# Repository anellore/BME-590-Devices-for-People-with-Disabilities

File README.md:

# BME-590-Devices-for-People-with-Disabilities

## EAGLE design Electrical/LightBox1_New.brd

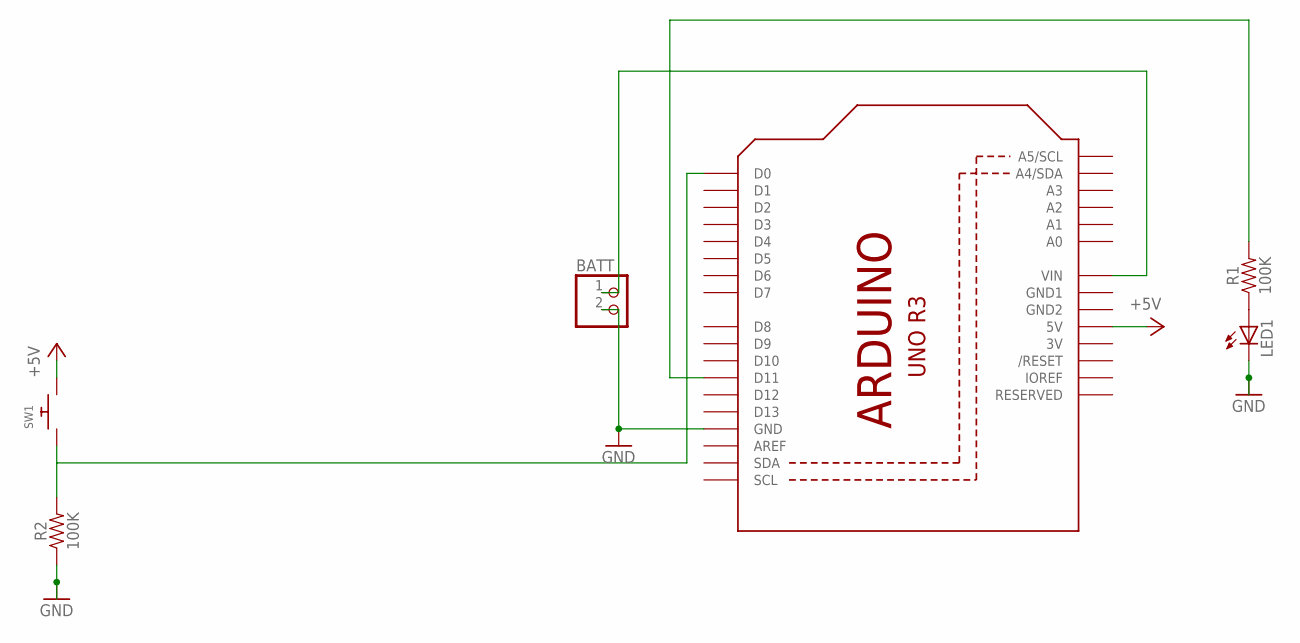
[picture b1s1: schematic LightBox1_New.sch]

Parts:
BATT: PINHD-1X2; 1X02
LED1: LED3MM
R1, R2: 100K; 0402
SW1: SWITCH_PUSHBUTTONSOFTTOUCHSMD_SJ; PUSHBUTTON_SMD_SJ
U1: ARDUINOR3-DIMENSION; ARDUINOR3

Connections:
3V: U1.3V
+5V: SW1.P$2, U1.5V
GND: BATT.2, LED1.K (C), R2.1, U1.GND
GND1: U1.GND1
GND2: U1.GND2
unnamed: BATT.1, U1.VIN
unnamed: R2.2, SW1.P$1, U1.D0
unnamed: R1.2, U1.D11
unnamed: LED1.A, R1.1

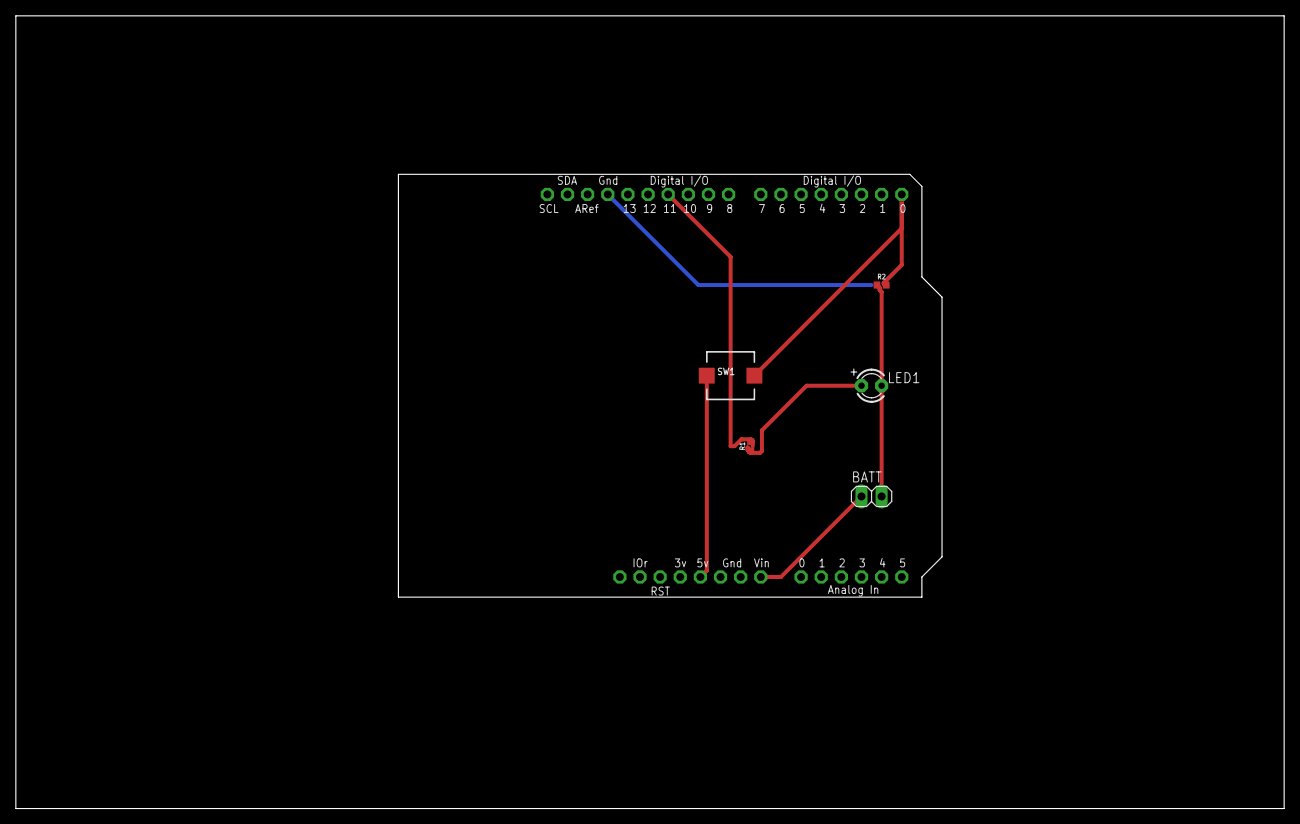
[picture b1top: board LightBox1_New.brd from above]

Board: 2 copper layers, 160.0 x 100.0 mm, 6 parts (0 on the bottom side), 6 nets.

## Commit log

2018-11-02 Circuit diagram commit
2018-11-08 Circuit Diagram EDA and Software for Light Switch
2018-11-08 Light Switch Schematic Board
2018-11-19 Going to create a mechanical directory eventually
2018-11-19 v.0.3.0
2018-11-27 Most recent light box
2018-12-02 Submission of boards to be etched
2018-12-14 Final Mechanical and Software Commit for Light Box
    The mechanical commit is not the same as the enclosure I ended up with in my final video. I didn't like my final CAD creations so I ended up using scrap parts from the Foundry.

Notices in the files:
parts and their libraries:
SparkFun-Resistors: Licensing: Creative Commons ShareAlike 4.0 International - https://creativecommons.org/licenses/by-sa/4.0
